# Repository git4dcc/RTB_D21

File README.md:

# RTB_D21

My Homebrew [D21](https://rtb4dcc.de/hardware/decoder/d21/) decoder is a double sided mobile decoder with Next18 (NEM-662) connector. The decoder is designed to integrate into the [RTB](https://rtb4dcc.de/concept/) digital control infrastructure.

<details>
<summary>See also</summary>

- [RTB_D12 - custom](/../../../../git4dcc/RTB_D12) (Fleischmann V100)
- [RTB_D13 - custom](/../../../../git4dcc/RTB_D13) (Minitrix coach)
- [RTB_D15 - custom](/../../../../git4dcc/RTB_D15) (Minitrix V160)
- [RTB_D16 - NEM651](/../../../../git4dcc/RTB_D16)
- [RTB_D20 - NEM651](/../../../../git4dcc/RTB_D20)
- [RTB_D22 - Plux16](/../../../../git4dcc/RTB_D22)
- [RTB_D23 - NEM652](/../../../../git4dcc/RTB_D23)

</details>

<details>
<summary>User Guides</summary>

- User Guide - DE
- [User Guide - EN](https://rtb4dcc.de/rtb_decoder_reference_en/)

</details>

<br>

## Decoder features
- **Next18** (NEM-662) connector
- **DCC**
  - DCC-A automatic logon
  - DCC-R protocol extension
  - Service Mode Programming
- **Railcom**
  - Channel 1/2
  - POM, xPOM
  - DYN: Speed, QoS, Track-voltage, Motor-current, AUX-current, Temp, Distance travelled
- Double sided
- Dimension: 15 x 9.5 mm
- 7-20V track voltage
- heartbeat LED
- adjustable max motor current (default 300mA)
- adjustable max AUX current (default 500mA)
- over temp protection
- Function output: LF/LR (dimmable, 1.4kHz) open drain
- Function output: AUX1/AUX2 (dimmable, 1.4kHz) open drain
- Function output: AUX3/AUX4 logic level or ZBCLK/ZBDAT
- Function output: AUX5/AUX6 logic level
- optional external buffer capacitor (max. 1500uF)
- <10mA idle power consumption
- SUSI3 (logic level)
- Firmware update over main tracks via DCC-R protocol

# Hardware
The current PCB layout uses SMD footprints with 0.5mm pitch and 0402 parts. Reflow soldering is recommended.

## PCB
- 6-layer PCB, FR4, 15 x 9.5 x 0.8mm (double sided)
- Power: 3.3V or 5V
- CPU: AVR64DD28
- Motor bridge: DRV8231
- Connector: Next18 (NEM-662)

## Kicad
[Schematic](doc/D21_schematic.pdf) | [Layout](doc/D21_layout.pdf)

<details>
<summary>Dependency</summary>
<br>

:yellow_circle: Requires my Kicad project library [RTB_SamacSys](https://github.com/git4dcc/RTB_SamacSys) in the same directory tree.

</details>

## Firmware
Filename structure: { **pcb** }{ **code** }{ **version** }.hex

Example: **D21F0001**.hex

|   | Description |
| --- | --- |
| **pcb** | Name of matching hardware (**D21**) |
| **code** | Type of code contained (**R**=rom, **B**=bootloader, **F**=flash, **U**=bld update, **P**=UPDI factory code) |
| **version** | Release version (**####**) |

[Firmware files](firmware)

## UPDI
The fuse settings as well as the P-code (D21Pxxxx.hex) has to be installed by using UPDI.<br>
Connecting the decoder via its track pins to a 5V(DC) power supply will boot its CPU. This way, its easy to program the fuses and flash.

<details>
<summary>Details</summary>

| Fuse Setting | P-code Install |
| --- | --- |
|||

</details>

# Images
| top | bottom |
| --- | --- |
|  |  |

# YouTube
Some YouTubes to see the D21 motor driver in action.<br><br>

This project is intended for hobby use only and is distributed in accordance with the Apache License 2.0 agreement.

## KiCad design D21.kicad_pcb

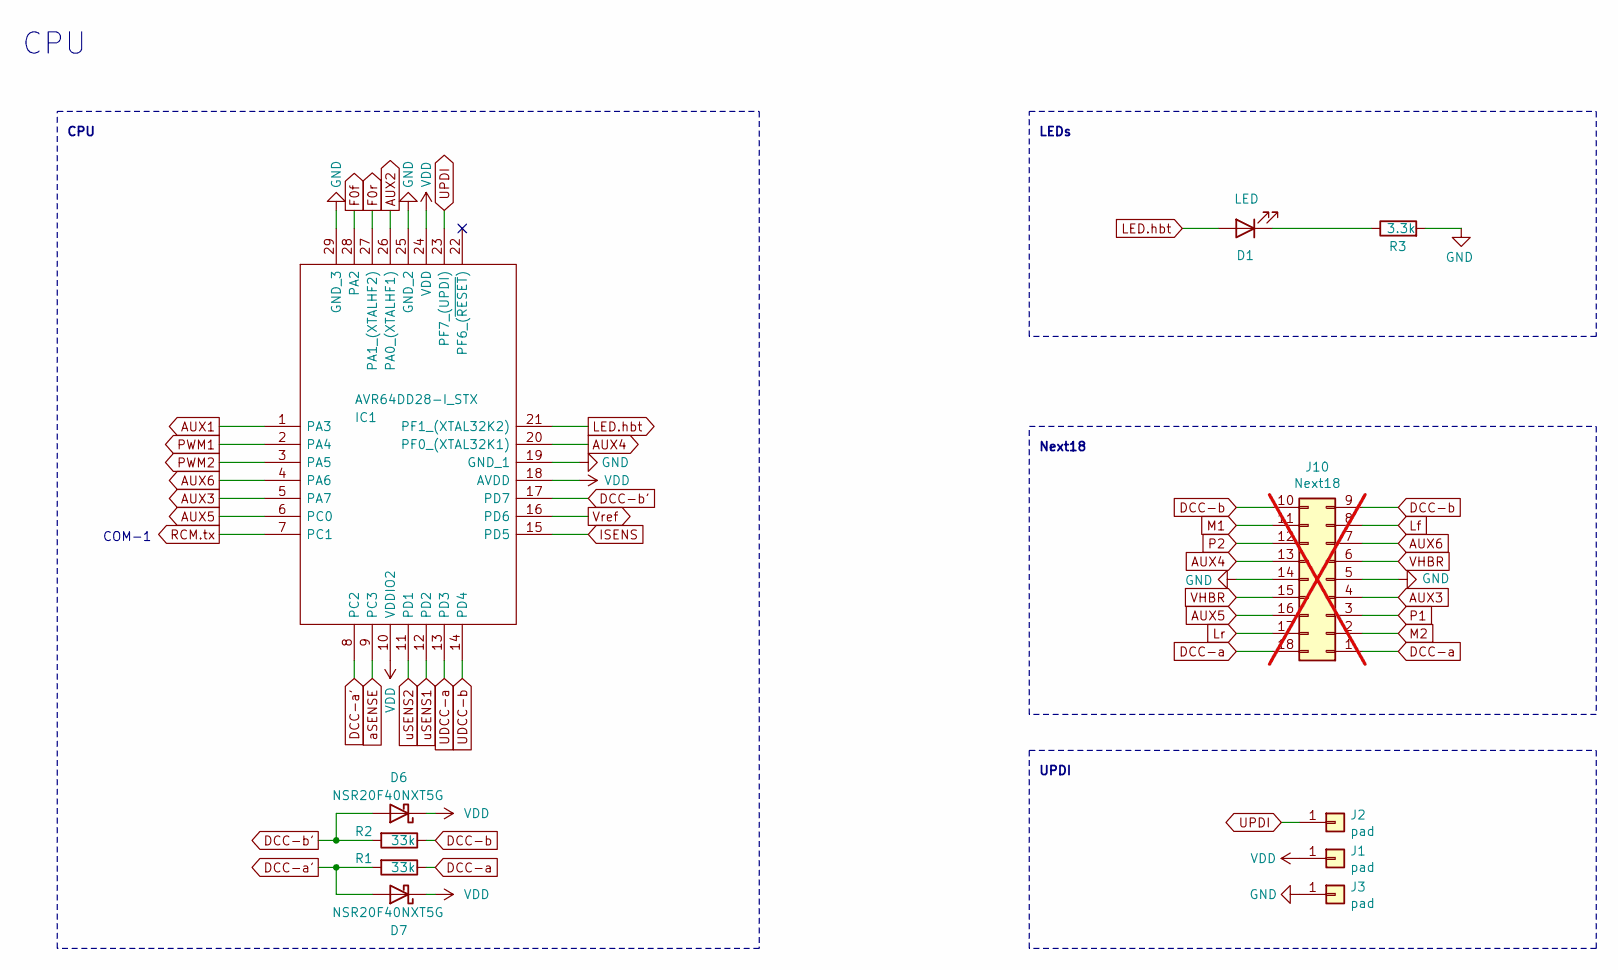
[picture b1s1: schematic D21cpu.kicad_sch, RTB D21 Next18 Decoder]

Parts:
D1: LED; LED_0402_1005Metric; LCSC Part # C130724
D6, D7: NSR20F40NXT5G; LCSC Part # C153761
IC1: AVR64DD28-I_STX; QFN-28-1EP_4x4mm_P0.4mm_EP2.3x2.3mm; LCSC Part # C5156221
J1, J2, J3: pad; Solder 0.8 x 0.5
J10: Next18; AXK6F16347YG; not fitted
R1, R2: 33k; R_0402_1005Metric; LCSC Part # C25779
R3: 3.3k; R_0402_1005Metric; LCSC Part # C25900

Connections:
AUX1: IC1.1 (PA3); also elsewhere on the board
AUX2: IC1.26 (PA0_(XTALHF1)); also elsewhere on the board
AUX3: IC1.5 (PA7), J10.4
AUX4: IC1.20 (PF0_(XTAL32K1)), J10.13
AUX5: IC1.6 (PC0), J10.16
AUX6: IC1.4 (PA6), J10.7
DCC-a: J10.1, J10.18, R1.1; also elsewhere on the board
DCC-a': D7.2 (A), IC1.8 (PC2), R1.2
DCC-b: J10.9, J10.10, R2.1; also elsewhere on the board
DCC-b': D6.2 (A), IC1.17 (PD7), R2.2
F0f: IC1.28 (PA2); also elsewhere on the board
F0r: IC1.27 (PA1_(XTALHF2)); also elsewhere on the board
GND: IC1.19 (GND_1), IC1.25 (GND_2), IC1.29 (GND_3), J3.1 (Pin_1_1), J10.5, J10.14, R3.2; also elsewhere on the board
ISENS: IC1.15 (PD5); also elsewhere on the board
LED.hbt: D1.2 (A), IC1.21 (PF1_(XTAL32K2))
Lf: J10.8; also elsewhere on the board
Lr: J10.17; also elsewhere on the board
M1: J10.11; also elsewhere on the board
M2: J10.2; also elsewhere on the board
unnamed: D1.1 (K), R3.1
P1: J10.3; also elsewhere on the board
P2: J10.12; also elsewhere on the board
PWM1: IC1.2 (PA4); also elsewhere on the board
PWM2: IC1.3 (PA5); also elsewhere on the board
RCM.tx: IC1.7 (PC1); also elsewhere on the board
UDCC-a: IC1.13 (PD3); also elsewhere on the board
UDCC-b: IC1.14 (PD4); also elsewhere on the board
UPDI: IC1.23 (PF7_(UPDI)), J2.1 (Pin_1_1)
VDD: D6.1 (K), D7.1 (K), IC1.10 (VDDIO2), IC1.18 (AVDD), IC1.24 (VDD), J1.1 (Pin_1_1); also elsewhere on the board
VHBR: J10.6, J10.15; also elsewhere on the board
Vref: IC1.16 (PD6); also elsewhere on the board
aSENSE: IC1.9 (PC3); also elsewhere on the board
uSENS1: IC1.12 (PD2); also elsewhere on the board
uSENS2: IC1.11 (PD1); also elsewhere on the board

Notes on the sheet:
UPDI
CPU
LEDs
Next18
COM-1

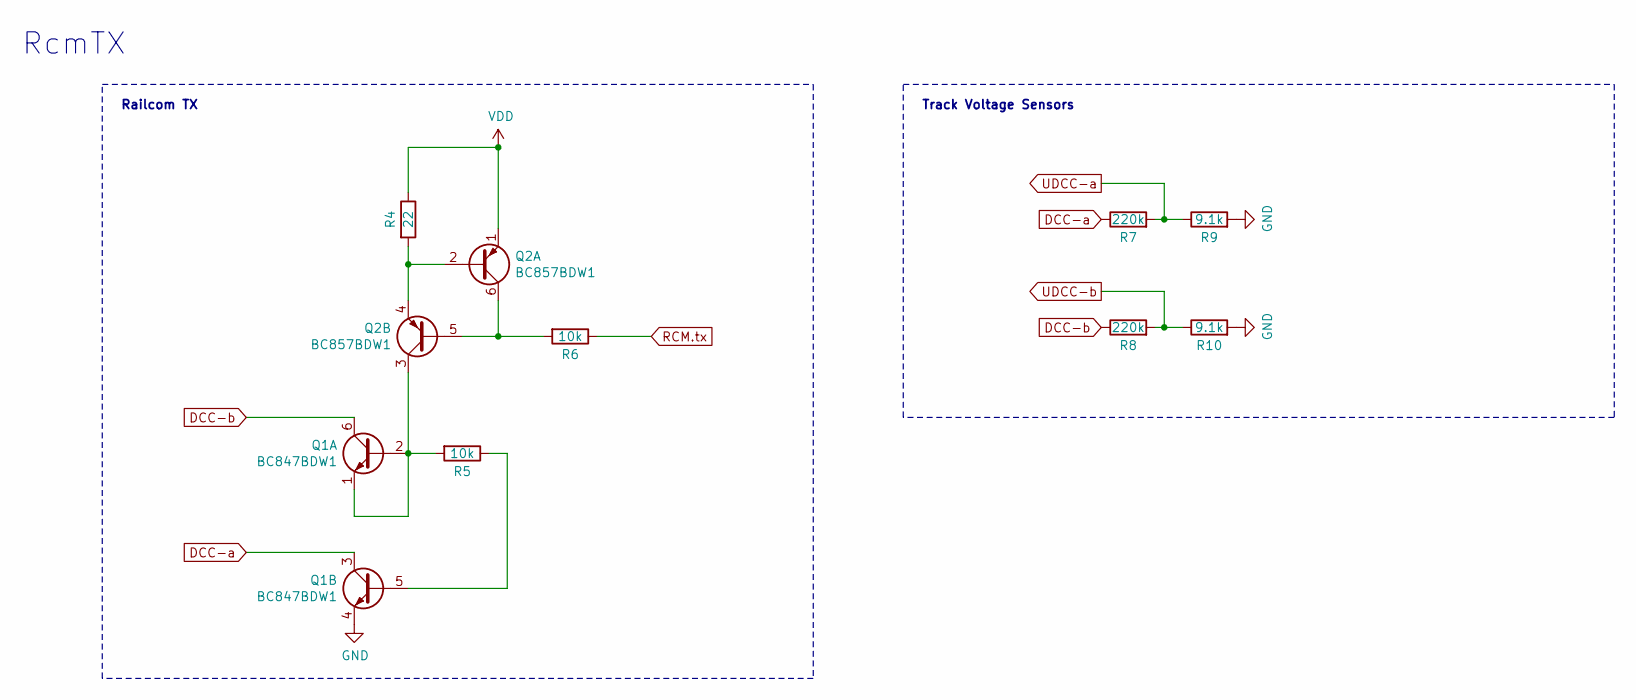
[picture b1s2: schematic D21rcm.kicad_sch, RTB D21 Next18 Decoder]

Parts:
Q1: BC847BDW1; SOT-666; LCSC Part # C455062
Q2: BC857BDW1; SOT-666; LCSC Part # C282521
R4: 22; R_0402_1005Metric; LCSC Part # C25092
R5, R6: 10k; R_0402_1005Metric; LCSC Part # C25744
R7, R8: 220k; R_0402_1005Metric; LCSC Part # C25767
R9, R10: 9.1k; R_0402_1005Metric; LCSC Part # C25926

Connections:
DCC-a: Q1.3 (C2), R7.1; also elsewhere on the board
DCC-b: Q1.6 (C1), R8.1; also elsewhere on the board
GND: Q1.4 (E2), R9.2, R10.2; also elsewhere on the board
unnamed: Q1.1 (E1), Q1.2 (B1), Q2.3 (C2), R5.2
unnamed: Q1.5 (B2), R5.1
unnamed: Q2.2 (B1), Q2.4 (E2), R4.2
unnamed: Q2.5 (B2), Q2.6 (C1), R6.2
RCM.tx: R6.1; also elsewhere on the board
UDCC-a: R7.2, R9.1; also elsewhere on the board
UDCC-b: R8.2, R10.1; also elsewhere on the board
VDD: Q2.1 (E1), R4.1; also elsewhere on the board

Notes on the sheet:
RcmTX
Railcom TX
Track Voltage Sensors

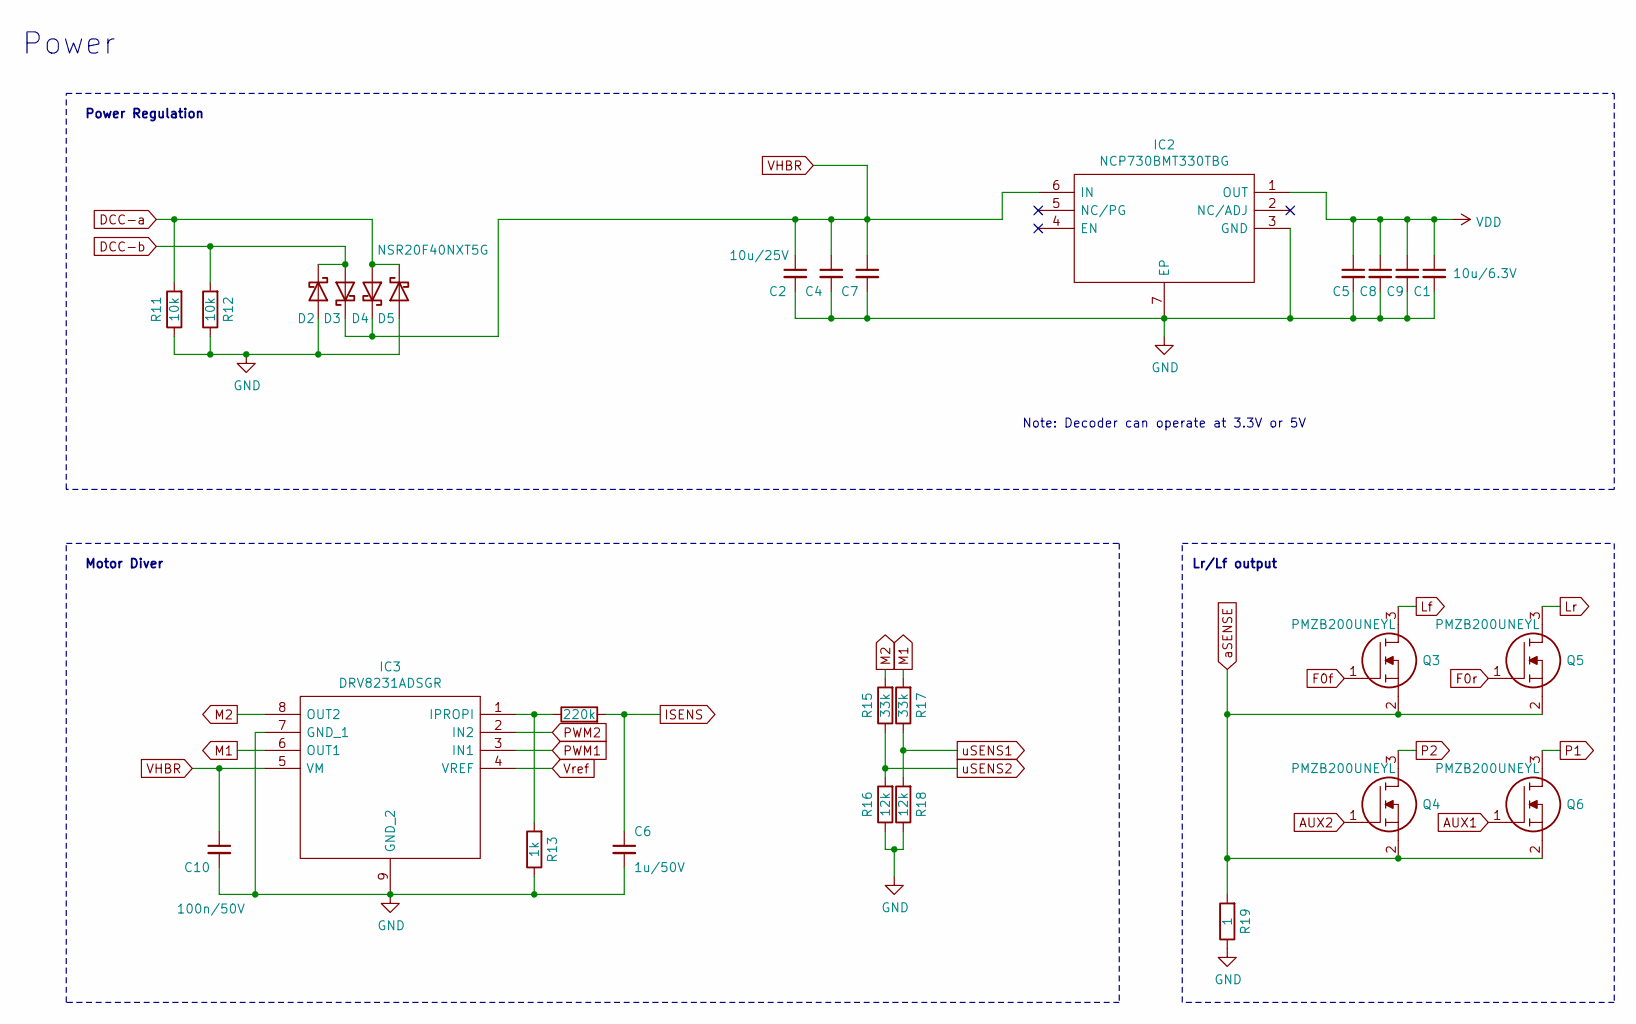
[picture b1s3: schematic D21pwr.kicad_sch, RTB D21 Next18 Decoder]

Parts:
C1, C5, C8, C9: 10u/6.3V; C_0402_1005Metric; LCSC Part # C15525
C2, C4, C7: 10u/25V; C_0603_1608Metric; LCSC Part # C96446
C6: 1u/50V; C_0402_1005Metric; LCSC Part # C52923
C10: 100n/50V; C_0402_1005Metric; LCSC Part # C307331
D2, D3, D4, D5: NSR20F40NXT5G; LCSC Part # C153761
IC2: NCP730BMT330TBG; WSON-6-1EP_2x2mm_P0.65mm_EP1x1.6mm_ThermalVias; LCSC Part # C892821
IC3: DRV8231ADSGR; SON50P200X200X80-9N; LCSC Part # C5139865
Q3, Q4, Q5, Q6: PMZB200UNEYL; Diodes_DFN1006-3; LCSC Part # C547292
R11, R12: 10k; R_0402_1005Metric; LCSC Part # C25744
R13: 1k; R_0402_1005Metric; LCSC Part # C11702
R14: 220k; R_0402_1005Metric; LCSC Part # C25767
R15, R17: 33k; R_0402_1005Metric; LCSC Part # C25779
R16, R18: 12k; R_0402_1005Metric; LCSC Part # C25752
R19: 1; R_0402_1005Metric; LCSC Part # C4346165

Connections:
AUX1: Q6.1; also elsewhere on the board
AUX2: Q4.1; also elsewhere on the board
DCC-a: D4.2 (A), D5.1 (K), R11.2; also elsewhere on the board
DCC-b: D2.1 (K), D3.2 (A), R12.2; also elsewhere on the board
F0f: Q3.1; also elsewhere on the board
F0r: Q5.1; also elsewhere on the board
GND: C1.2, C2.2, C4.2, C5.2, C6.2, C7.2, C8.2, C9.2, C10.2, D2.2 (A), D5.2 (A), IC2.3 (GND), IC2.7 (EP), IC3.7 (GND_1), IC3.9 (GND_2), R11.1, R12.1, R13.1, R16.1, R18.1, R19.1; also elsewhere on the board
ISENS: C6.1, R14.2; also elsewhere on the board
Lf: Q3.3; also elsewhere on the board
Lr: Q5.3; also elsewhere on the board
M1: IC3.6 (OUT1), R17.2; also elsewhere on the board
M2: IC3.8 (OUT2), R15.2; also elsewhere on the board
unnamed: IC3.1 (IPROPI), R13.2, R14.1
P1: Q6.3; also elsewhere on the board
P2: Q4.3; also elsewhere on the board
PWM1: IC3.3 (IN1); also elsewhere on the board
PWM2: IC3.2 (IN2); also elsewhere on the board
VDD: C1.1, C5.1, C8.1, C9.1, IC2.1 (OUT); also elsewhere on the board
VHBR: C2.1, C4.1, C7.1, C10.1, D3.1 (K), D4.1 (K), IC2.6 (IN), IC3.5 (VM); also elsewhere on the board
Vref: IC3.4 (VREF); also elsewhere on the board
aSENSE: Q3.2, Q4.2, Q5.2, Q6.2, R19.2; also elsewhere on the board
uSENS1: R17.1, R18.2; also elsewhere on the board
uSENS2: R15.1, R16.2; also elsewhere on the board

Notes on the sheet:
Power
Motor Diver
Lr/Lf output
Power Regulation
Note: Decoder can operate at 3.3V or 5V

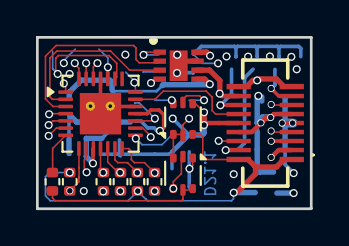
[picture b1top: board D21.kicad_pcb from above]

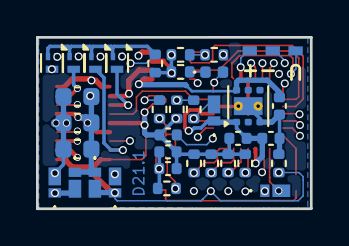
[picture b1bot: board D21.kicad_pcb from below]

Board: 6 copper layers, 15.2 x 9.5 mm, 48 parts (37 on the bottom side), 39 nets.

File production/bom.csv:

Designator,Footprint,Quantity,Value,LCSC Part #
"C1, C5, C8, C9",0402,4,10u/6.3V,C15525
C10,0402,1,100n/50V,C307331
"C2, C4, C7",0603,3,10u/25V,C96446
C6,0402,1,1u/50V,C52923
D1,0402,1,LED,C130724
"D2, D3, D4, D5, D6, D7",NSR20F40NXT5G,6,NSR20F40NXT5G,C153761
IC1,QFN-28-1EP_4x4mm_P0.4mm_EP2.3x2.3mm,1,AVR64DD28-I_STX,C5156221
IC2,WSON-6-1EP_2x2mm_P0.65mm_EP1x1.6mm_ThermalVias,1,NCP730BMT330TBG,C892821
IC3,SON50P200X200X80-9N,1,DRV8231ADSGR,C5139865
"J1, J2, J3",Solder 0.8 x 0.5,3,pad,
J10,AXK6F16347YG,1,Next18,
Q1,SOT-666,1,BC847BDW1,C455062
Q2,SOT-666,1,BC857BDW1,C282521
"Q3, Q4, Q5, Q6",Diodes_DFN1006-3,4,PMZB200UNEYL,C547292
"R1, R15, R17, R2",0402,4,33k,C25779
"R10, R9",0402,2,9.1k,C25926
"R11, R12, R5, R6",0402,4,10k,C25744
R13,0402,1,1k,C11702
"R14, R7, R8",0402,3,220k,C25767
"R16, R18",0402,2,12k,C25752
R19,0402,1,1,C4346165
R3,0402,1,3.3k,C25900
R4,0402,1,22,C25092

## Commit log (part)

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2024-11-15 initial
2025-03-22 add: decoder lock
2025-07-31 add: fuses
2025-07-31 add: updi description
2025-08-05 mod: led automation
2025-10-02 fix: SUSI/AUX
2026-02-20 Update links in README.md to relative paths
2026-02-20 git mirror test
2026-06-26 updated Kicad version

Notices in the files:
D21.kicad_pcb:
Licensed under the Apache License, Version 2
